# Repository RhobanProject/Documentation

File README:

The full documentation is managed here :
https://sites.google.com/site/rhobanyeosuproject/

It will be moved here later

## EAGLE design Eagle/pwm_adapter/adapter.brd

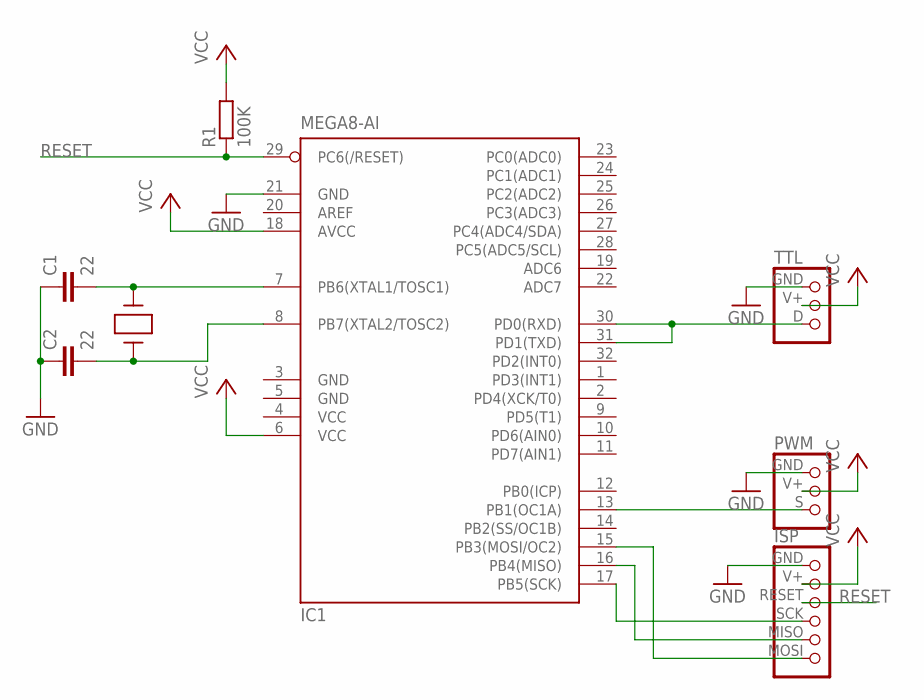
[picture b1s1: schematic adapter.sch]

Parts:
C1, C2: 22; C0603
IC1: MEGA8-AI; TQFP32-08
ISP: CONNEC_1X06_AVRISP; CONNEC_AVRISP
PWM: CONNEC_1X03_PWM; CONNEC_PWM
R1: 100K; R0805
TTL: CONNEC_1X03_TTL; CONNEC_TTL
XTAL: QUARTZ; HC49US

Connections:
DATA: IC1.30 (PD0(RXD)), IC1.31 (PD1(TXD)), TTL.D (3)
GND: C1.1, C2.1, IC1.3 (GND), IC1.5 (GND), IC1.21 (GND), ISP.GND (1), PWM.GND (1), TTL.GND (1)
MISO: IC1.16 (PB4(MISO)), ISP.MISO (5)
MOSI: IC1.15 (PB3(MOSI/OC2)), ISP.MOSI (6)
unnamed: C1.2, IC1.7 (PB6(XTAL1/TOSC1)), XTAL.2
unnamed: C2.2, IC1.8 (PB7(XTAL2/TOSC2)), XTAL.1
OC1A: IC1.13 (PB1(OC1A)), PWM.S (3)
RESET: IC1.29 (PC6(/RESET)), ISP.RESET (3), R1.1
SCK: IC1.17 (PB5(SCK)), ISP.SCK (4)
VCC: IC1.4 (VCC), IC1.6 (VCC), IC1.18 (AVCC), ISP.V+ (2), PWM.V+ (2), R1.2, TTL.V+ (2)

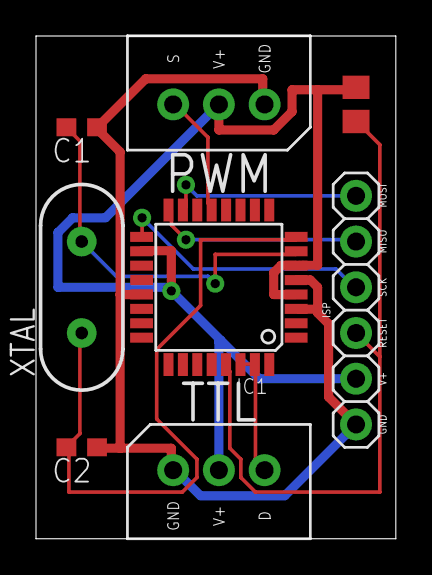
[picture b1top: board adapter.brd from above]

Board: 2 copper layers, 20.0 x 27.9 mm, 8 parts (0 on the bottom side), 10 nets.

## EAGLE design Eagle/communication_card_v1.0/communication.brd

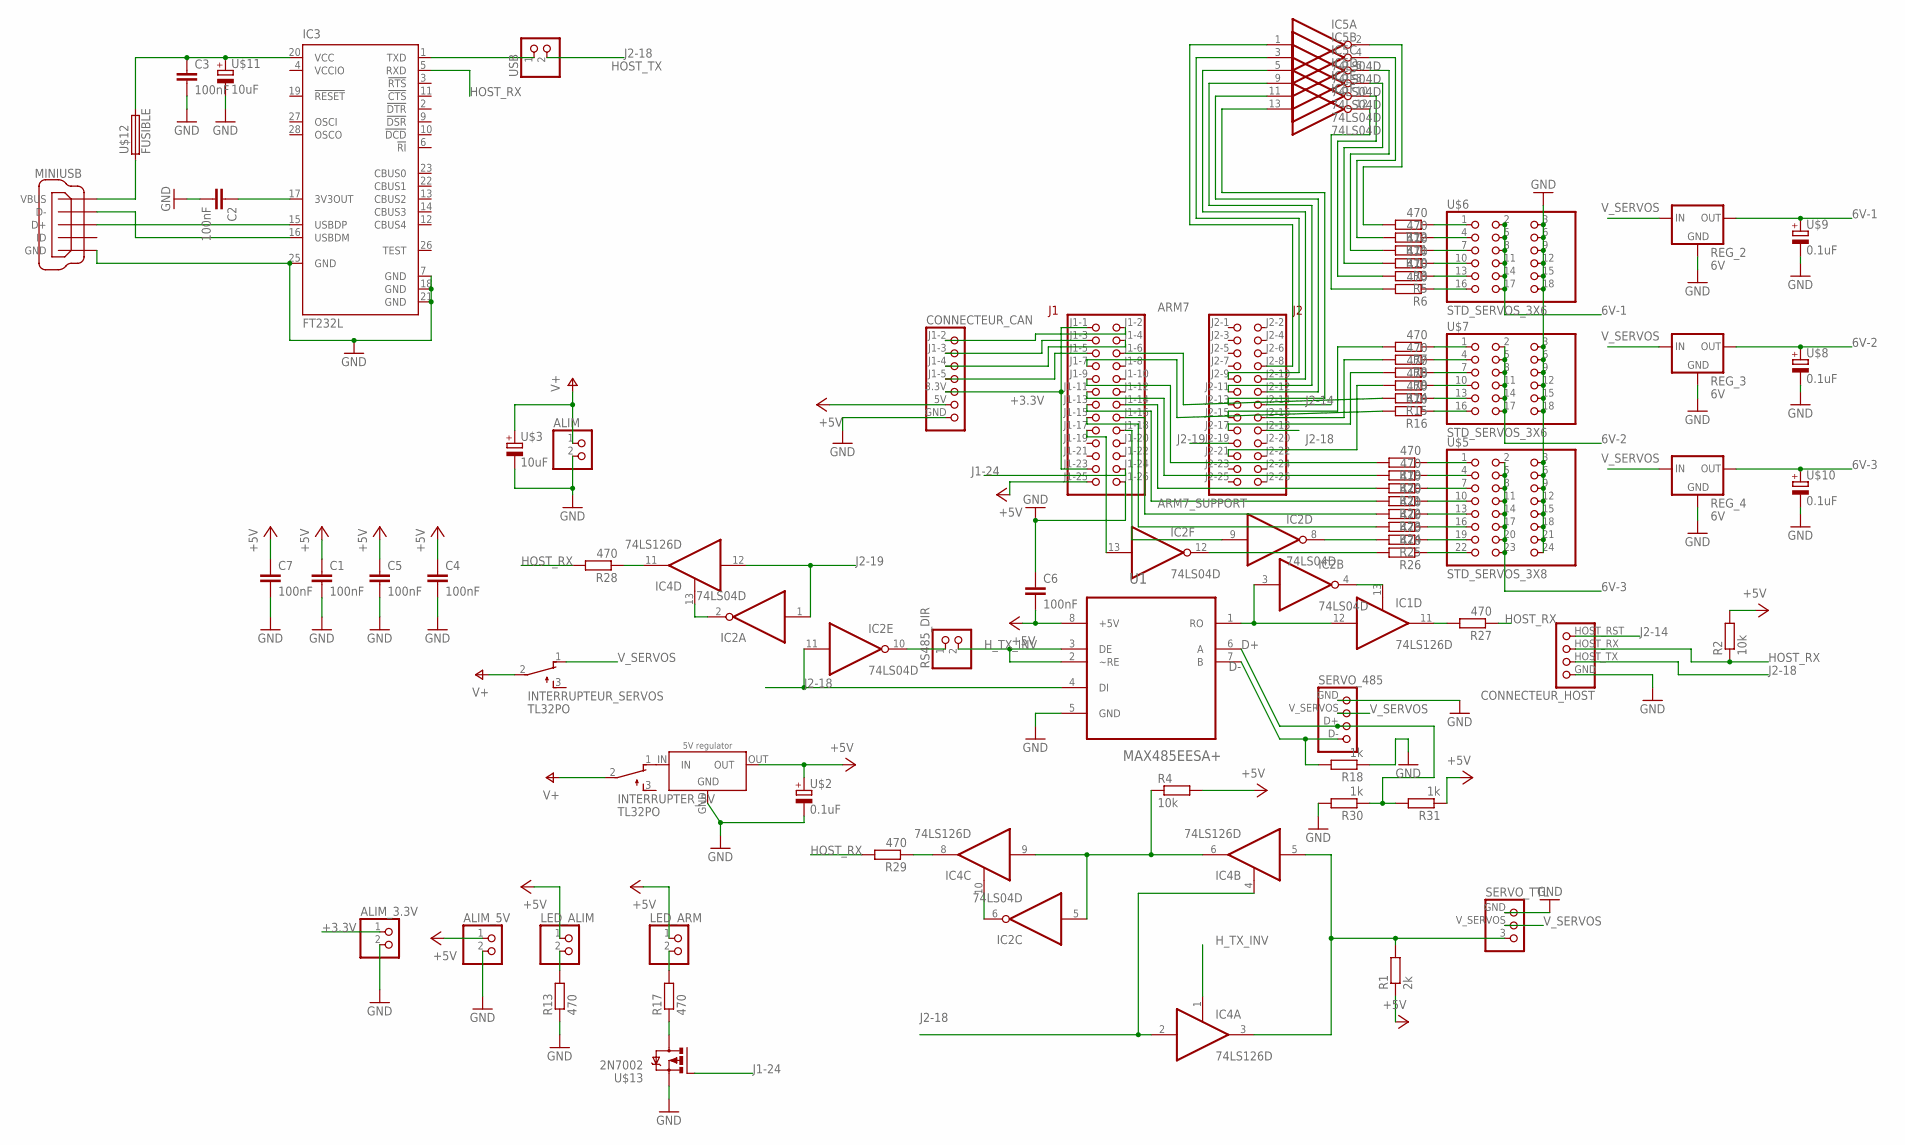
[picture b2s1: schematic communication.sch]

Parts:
ALIM: CONNEC_1X02
ALIM_3.3V, ALIM_5V: CONNEC_1X02
ARM7: ARM7_SUPPORT
C1, C2, C3, C4, C5, C6, C7: 100nF; C1210
CONNECTEUR_CAN: CONNECTEUR_CAN
CONNECTEUR_HOST: CONNECTEUR_HOST
IC1, IC4: 74LS126D; SO14
IC2, IC5: 74LS04D; SO14
IC3: FT232L; SSOP28
INTERRUPTER_5V: TL32PO; TL3XPO
INTERRUPTEUR_SERVOS: TL32PO; TL3XPO
LED_ALIM: CONNEC_1X02
LED_ARM: CONNEC_1X02
MINIUSB: MINIUSB; MINI_USB
R1: 2k; R0805
R2, R4: 10k; R0805
R3, R5, R6, R7, R8, R9, R10, R11, R12, R13, R14, R15, R16, R17, R19, R20, R21, R22, R23, R24, R25, R26, R27, R28, R29: 470; R0805
R18, R30, R31: 1k; R0805
REG_2, REG_3, REG_4: 6V; 78XXL
RS485_DIR: CONNEC_1X02
SERVO_485: CONNECTEUR_485
SERVO_TTL: CONNECTEUR_TTL
U1: MAX485EESA+; SOIC127P600X175-8N
U$2, U$8, U$9, U$10: 0.1uF; E2,5-6
U$3, U$11: 10uF; E5-10,5
U$5: STD_SERVOS_3X8
U$6, U$7: STD_SERVOS_3X6
U$12: FUSIBLE
U$13: 2N7002; SOT23
U$14: 5V regulator; REGULATEUR_CMS
USB: CONNEC_1X02

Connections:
6V-1: REG_2.OUT, U$6.2, U$6.5, U$6.8, U$6.11, U$6.14, U$6.17, U$9.+
6V-2: REG_3.OUT, U$7.2, U$7.5, U$7.8, U$7.11, U$7.14, U$7.17, U$8.+
6V-3: REG_4.OUT, U$5.2, U$5.5, U$5.8, U$5.11, U$5.14, U$5.17, U$5.20, U$5.23, U$10.+
+3.3V: ALIM_3.3V.1, ARM7.J1-1 (1), ARM7.J1-23 (23), CONNECTEUR_CAN.3.3V
+5V: ALIM_5V.1, ARM7.J1-25 (25), C1.1, C4.1, C5.1, C6.2, C7.1, CONNECTEUR_CAN.5V, IC1.14 (+5V), IC2.14 (+5V), IC4.14 (+5V), IC5.14 (+5V), LED_ALIM.1, LED_ARM.1, R1.1, R2.2, R4.2, R31.1, U1.8 (+5V), U$2.+, U$14.OUT
ALIM_USB: C3.1, IC3.20 (VCC), U$11.+, U$12.P$2 (2)
B$1: ARM7.J2-8 (34), IC5.1 (I)
B$2: ARM7.J2-9 (35), IC5.3 (I)
B$3: ARM7.J2-10 (36), IC5.5 (I)
B$4: ARM7.J2-11 (37), IC5.9 (I)
B$5: ARM7.J2-12 (38), IC5.11 (I)
B$6: ARM7.J2-13 (39), IC5.13 (I)
B$7: ARM7.J2-15 (41), R7.2
B$8: ARM7.J2-16 (42), R8.2
B$9: ARM7.J2-17 (43), R9.2
B$10: ARM7.J2-21 (47), R14.2
B$11: ARM7.J1-6 (6), R15.2
B$12: ARM7.J1-7 (7), R16.2
D+: R30.1, R31.2, SERVO_485.D+, U1.6 (A)
D-: R18.2, SERVO_485.D-, U1.7 (B)
GND: ALIM.2, ALIM_3.3V.2, ALIM_5V.2, ARM7.J1-26 (26), C1.2, C2.2, C3.2, C4.2, C5.2, C6.1, C7.2, CONNECTEUR_CAN.GND, CONNECTEUR_HOST.GND, IC1.7 (GND), IC2.7 (GND), IC3.7 (GND), IC3.18 (GND), IC3.21 (GND), IC3.25 (GND), IC4.7 (GND), IC5.7 (GND), MINIUSB.GND, R13.1, R18.1, R30.2, REG_2.GND, REG_3.GND, REG_4.GND, SERVO_485.GND, SERVO_TTL.GND, U1.5 (GND), U$2.-, U$3.-, U$5.3, U$5.6, U$5.9, U$5.12, U$5.15, U$5.18, U$5.21, U$5.24, U$6.3, U$6.6, U$6.9, U$6.12, U$6.15, U$6.18, U$7.3, U$7.6, U$7.9, U$7.12, U$7.15, U$7.18, U$8.-, U$9.-, U$10.-, U$11.-, U$13.2 (S), U$14.GND, U$14.GND2 (GND)
HOST_RX: CONNECTEUR_HOST.HOST_RX, IC3.5 (RXD), R2.1, R27.1, R28.2, R29.2
H_TX_INV: IC4.1 (OE), RS485_DIR.2, U1.2 (~RE), U1.3 (DE)
J1-2: ARM7.J1-2 (2), CONNECTEUR_CAN.J1-2
J1-3: ARM7.J1-3 (3), CONNECTEUR_CAN.J1-3
J1-4: ARM7.J1-4 (4), CONNECTEUR_CAN.J1-4
J1-5: ARM7.J1-5 (5), CONNECTEUR_CAN.J1-5
J1-24: ARM7.J1-24 (24), U$13.1 (G)
J2-14: ARM7.J2-14 (40), CONNECTEUR_HOST.HOST_RST
J2-18: ARM7.J2-18 (44), CONNECTEUR_HOST.HOST_TX, IC2.11 (I), IC4.2 (I), IC4.4 (OE), U1.4 (DI), USB.2
J2-19: ARM7.J2-19 (45), IC2.1 (I), IC4.12 (I)
unnamed: IC2.6 (O), IC4.10 (OE)
unnamed: IC2.5 (I), IC4.6 (O), IC4.9 (I), R4.1
unnamed: INTERRUPTER_5V.1 (O), U$14.IN
unnamed: IC2.8 (O), R25.2
unnamed: IC4.3 (O), IC4.5 (I), R1.2, SERVO_TTL.3
unnamed: LED_ALIM.2, R13.2
unnamed: IC1.12 (I), IC2.3 (I), U1.1 (RO)
unnamed: IC2.12 (O), R26.2
unnamed: R17.1, U$13.3 (D)
unnamed: LED_ARM.2, R17.2
unnamed: IC3.1 (TXD), USB.1
unnamed: IC1.13 (OE), IC2.4 (O)
unnamed: ARM7.J1-9 (9), R19.2
unnamed: MINIUSB.VBUS, U$12.P$1 (1)
unnamed: IC2.2 (O), IC4.13 (OE)
unnamed: R12.1, U$6.1
unnamed: R11.1, U$6.4
unnamed: R10.1, U$6.7
unnamed: R3.1, U$6.10
unnamed: R5.1, U$6.13
unnamed: R6.1, U$6.16
unnamed: R7.1, U$7.1
unnamed: R8.1, U$7.4
unnamed: R9.1, U$7.7
unnamed: R14.1, U$7.10
unnamed: R15.1, U$7.13
unnamed: R16.1, U$7.16
unnamed: ARM7.J1-11 (11), R20.2
unnamed: ARM7.J1-13 (13), R22.2
unnamed: ARM7.J1-14 (14), R21.2
unnamed: ARM7.J1-16 (16), R23.2
unnamed: ARM7.J1-15 (15), R24.2
unnamed: ARM7.J1-18 (18), IC2.9 (I)
unnamed: ARM7.J1-17 (17), IC2.13 (I)
unnamed: R19.1, U$5.1
unnamed: R20.1, U$5.4
unnamed: R21.1, U$5.7
unnamed: R22.1, U$5.10
unnamed: R23.1, U$5.13
unnamed: R24.1, U$5.16
unnamed: R25.1, U$5.19
unnamed: R26.1, U$5.22
unnamed: IC2.10 (O), RS485_DIR.1
unnamed: C2.1, IC3.17 (3V3OUT)
unnamed: IC3.15 (USBDP), MINIUSB.D+
unnamed: IC3.16 (USBDM), MINIUSB.D-
unnamed: IC5.12 (O), R6.2
unnamed: IC5.10 (O), R5.2
unnamed: IC5.8 (O), R3.2
unnamed: IC5.6 (O), R10.2
unnamed: IC5.4 (O), R11.2
unnamed: IC5.2 (O), R12.2
TO_RX-1: IC1.11 (O), R27.2
TO_RX-2: IC4.8 (O), R29.1
TO_RX-3: IC4.11 (O), R28.1
V+: ALIM.1, INTERRUPTER_5V.2, INTERRUPTEUR_SERVOS.2, U$3.+
VCCIO: IC3.4 (VCCIO)
V_SERVOS: INTERRUPTEUR_SERVOS.1 (O), REG_2.IN, REG_3.IN, REG_4.IN, SERVO_485.V_SERVOS, SERVO_TTL.V_SERVOS

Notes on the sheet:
HOST_TX

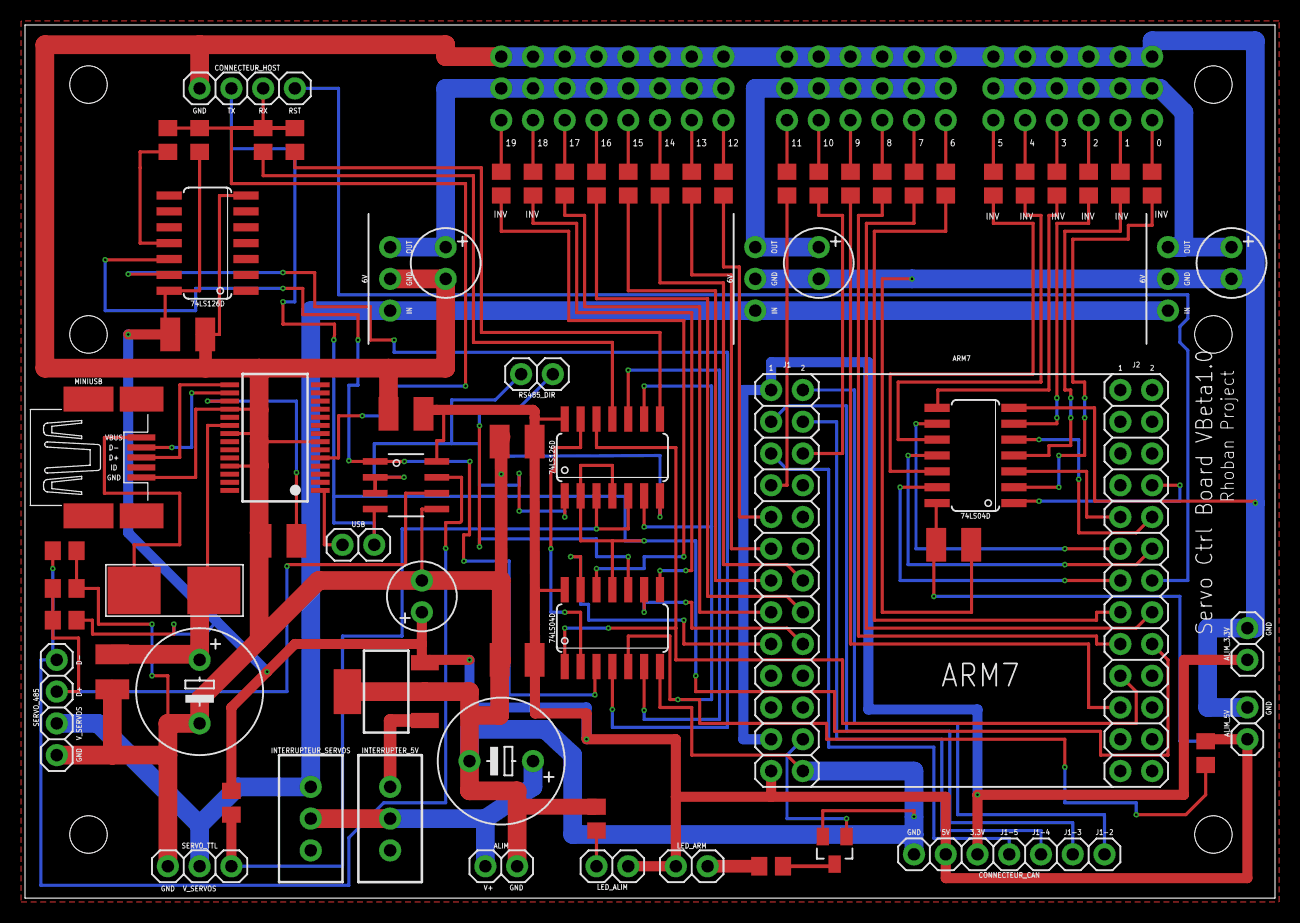
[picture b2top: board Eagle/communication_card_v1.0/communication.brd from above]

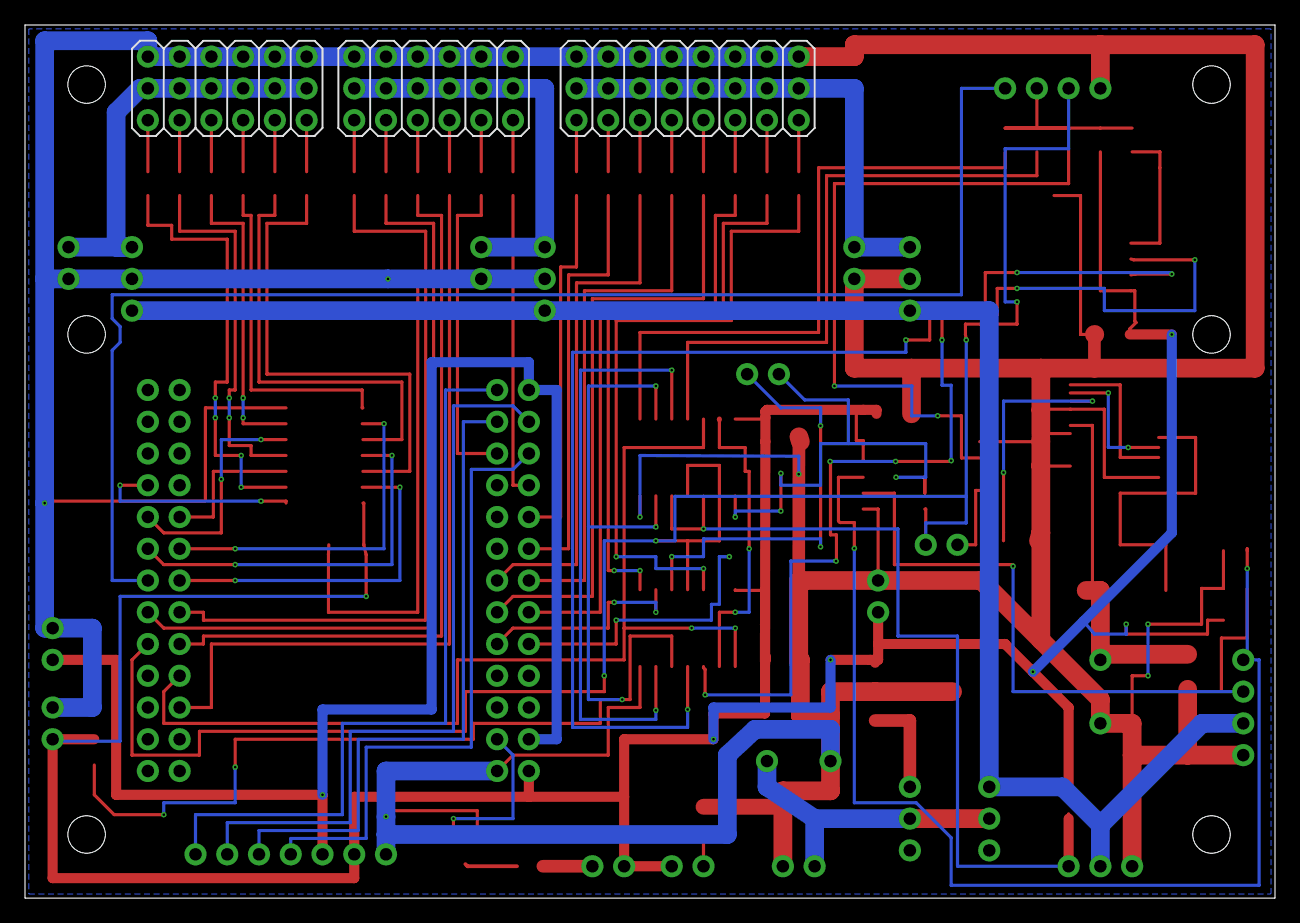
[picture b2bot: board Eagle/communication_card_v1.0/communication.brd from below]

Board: 2 copper layers, 100.0 x 69.9 mm, 74 parts (3 on the bottom side), 88 nets.

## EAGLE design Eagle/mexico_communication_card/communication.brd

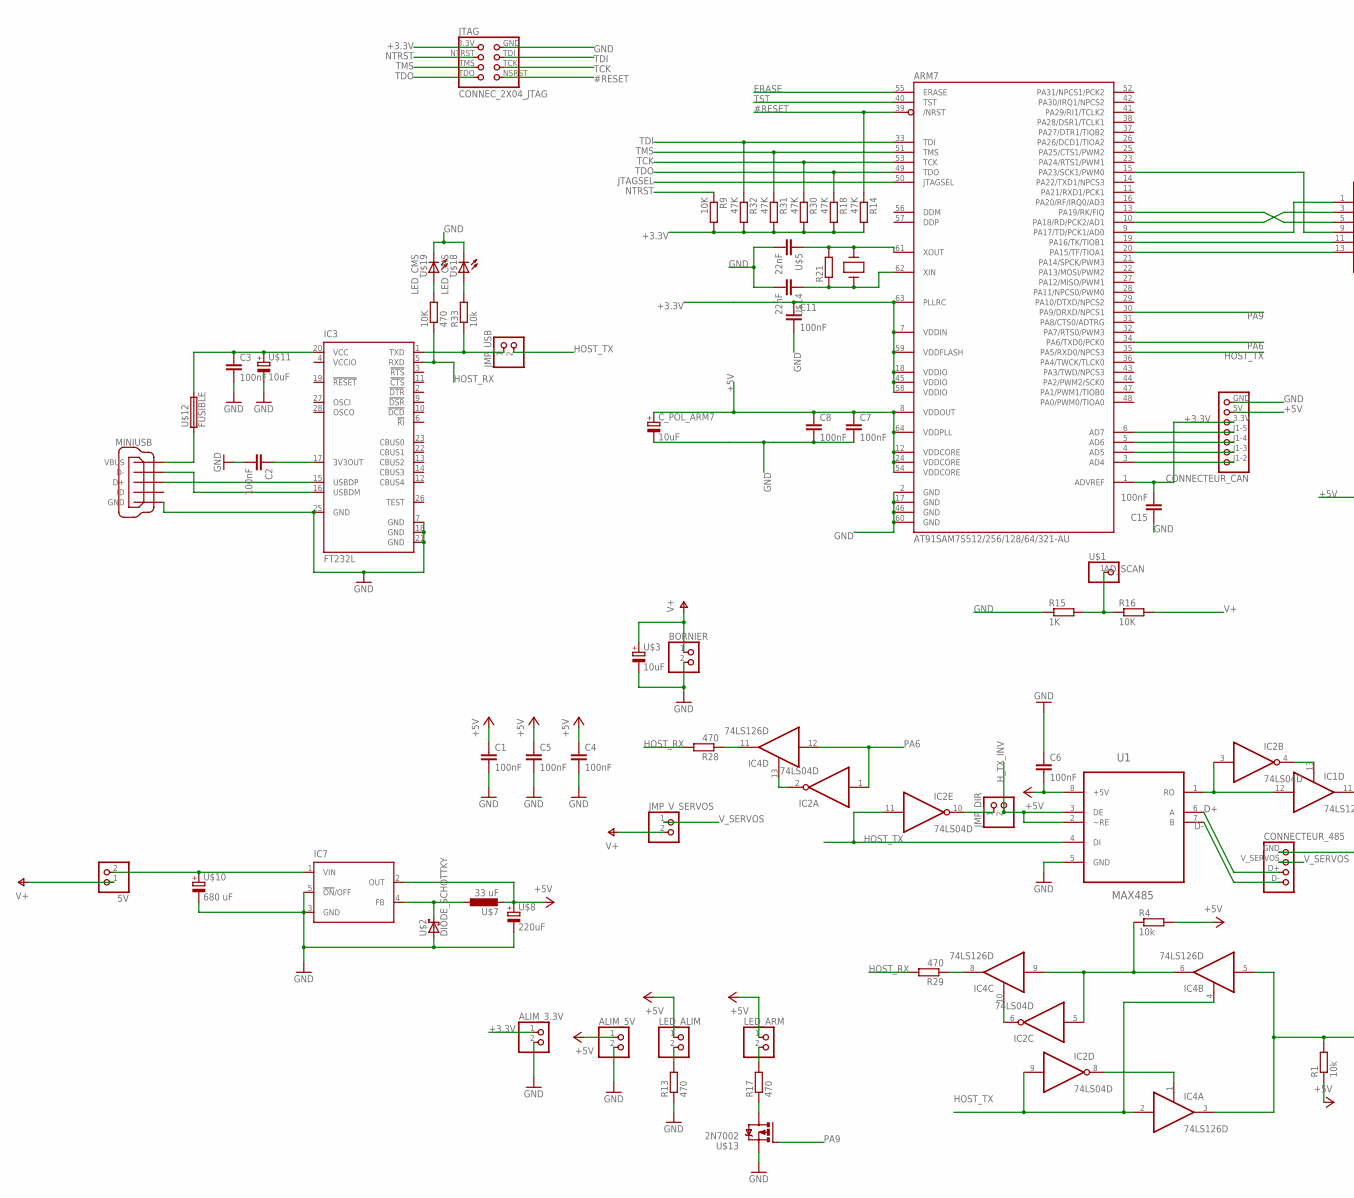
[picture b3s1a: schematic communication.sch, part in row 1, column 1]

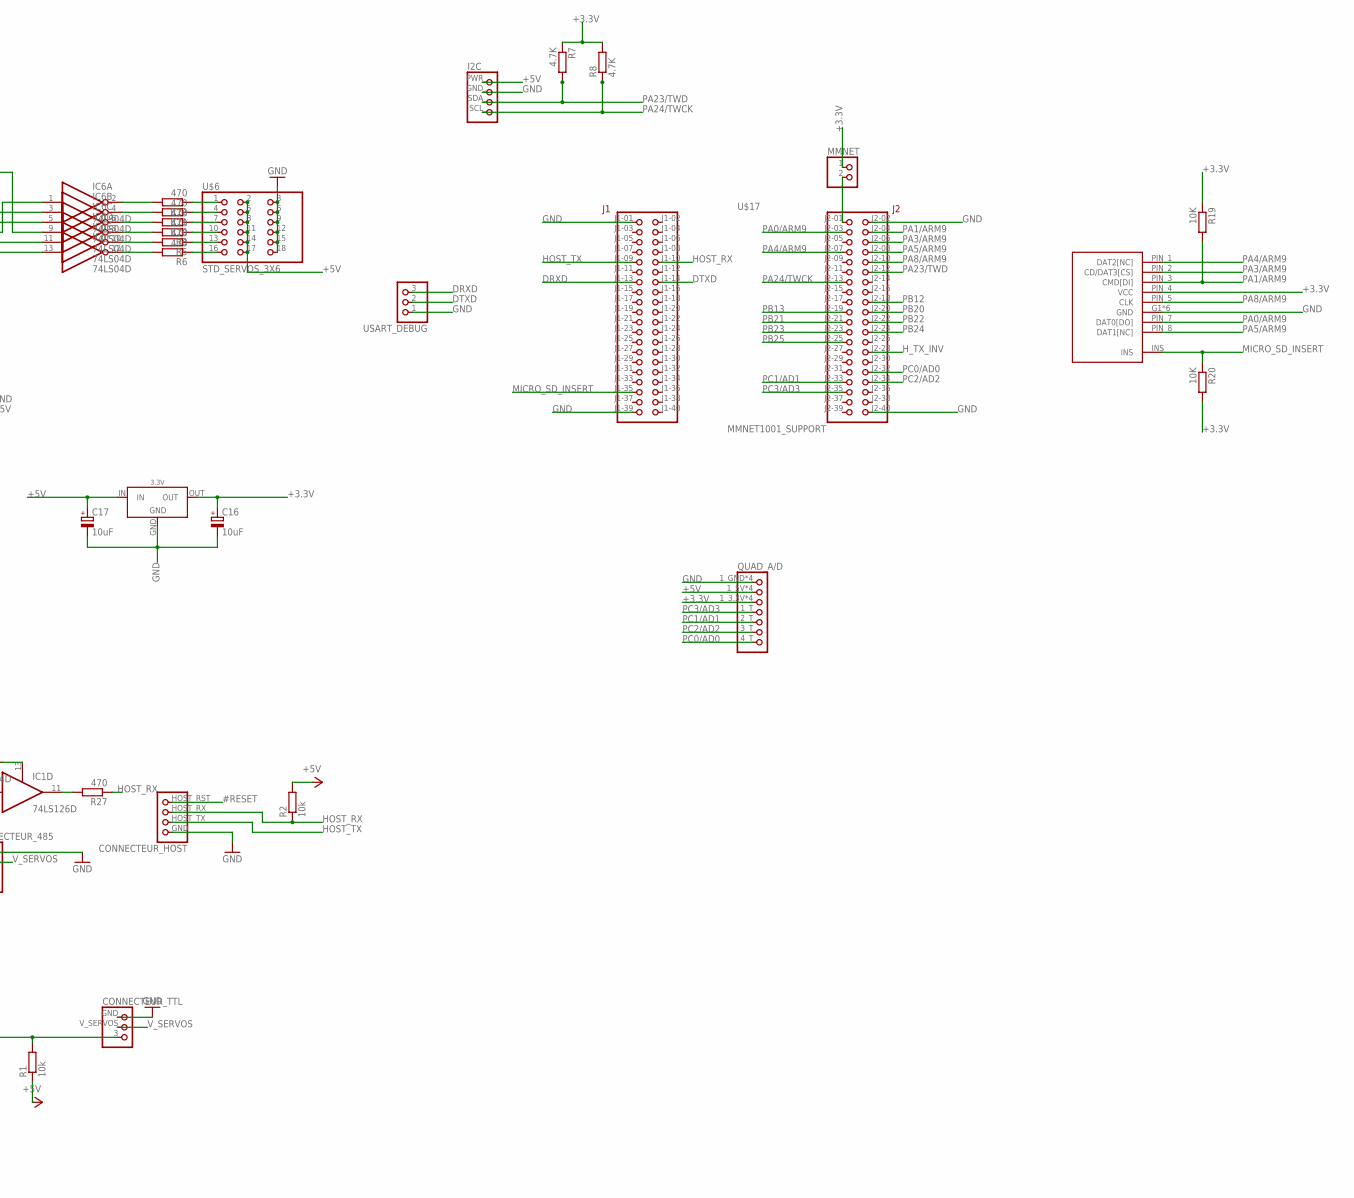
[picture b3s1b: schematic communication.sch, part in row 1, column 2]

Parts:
5V: CONNEC_1X02CONNEC_1X02_LARGE; CONNEC_ALIM
10K: 470; R0805@1
ALIM_3.3V, ALIM_5V: CONNEC_1X02
ARM7: AT91SAM7S512/256/128/64/321-AU; LQFP64
BORNIER: CONNEC_1X02CONNEC_1X02_LARGE; CONNEC_ALIM
C1, C2, C3, C4, C5, C6, C7, C8, C11, C15: 100nF; C0805
C16, C17: 10uF; PANASONIC_B
CONNECTEUR_485: CONNECTEUR_485
CONNECTEUR_CAN: CONNECTOR_CAN
CONNECTEUR_HOST: CONNECTEUR_HOST
CONNECTEUR_TTL: CONNECTEUR_TTL
C_POL_ARM7: 10uF; PANASONIC_B
I2C: CONNEC_1X04_I2C; CONNEC_I2C
IC1, IC4: 74LS126D; SO14
IC2, IC6: 74LS04D; SO14
IC3: FT232L; SSOP28
IC7: LM2596S; TO263-5
JMP_DIR: CONNEC_1X02
JMP_USB: CONNEC_1X02
JMP_V_SERVOS: CONNEC_1X02CONNEC_1X02_LARGE; CONNEC_ALIM
JTAG: CONNEC_2X04_JTAG; CONNEC_JTAG_MINIMAL
LED_ALIM: CONNEC_1X02
LED_ARM: CONNEC_1X02
MINIUSB: MINIUSB; MINI_USB
MMNET: CONNEC_1X02CONNEC_1X02_LARGE; CONNEC_ALIM
QUAD_A/D: QUAD_A/D
R1, R2, R4, R33: 10k; R0805@1
R3, R5, R6, R10, R11, R12, R13, R17, R27, R28, R29: 470; R0805@1
R7, R8: 4.7K; R0805@1
R9, R16, R19, R20: 10K; R0805@1
R14, R18, R30, R31, R32: 47K; R0805@1
R15: 1K; R0805@1
R21: RESISTANCE-1MOHM; R0805
U1: MAX485; SO8
U$1: CONNEC_1X01
U$2: DIODE_SCHOTTKY; SOD123W
U$3, U$11: 10uF; PANASONIC_B
U$4: 18.432 Mhz; ABLS
U$5, U$14: 22nF; C0603
U$6: STD_SERVOS_3X6
U$7: 33 uF; SDC0604
U$8: 220uF; E3,5-8
U$9: MICRO_SD
U$10: 680 uF; E3,5-8
U$12: FUSIBLE
U$13: 2N7002; SOT23
U$15: 3.3V; REGULATEUR_CMS
U$17: MMNET1001_SUPPORT; MMNET01_SUPPORT
U$18, U$19: LED_CMS
USART_DEBUG: CONNEC_1X03

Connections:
#RESET: ARM7.39 (/NRST), CONNECTEUR_HOST.HOST_RST, JTAG.NSRST (8), R14.1
+3.3V: ALIM_3.3V.1, ARM7.1 (ADVREF), ARM7.7 (VDDIN), ARM7.18 (VDDIO), ARM7.45 (VDDIO), ARM7.58 (VDDIO), ARM7.59 (VDDFLASH), ARM7.63 (PLLRC), C11.1, C15.2, C16.+, CONNECTEUR_CAN.3.3V, JTAG.3.3V (1), MMNET.1, QUAD_A/D.1_3.3V (3), QUAD_A/D.2_3.3V (3), QUAD_A/D.3_3.3V (3), QUAD_A/D.4_3.3V (3), R7.1, R8.2, R9.2, R14.2, R18.2, R19.1, R20.2, R30.2, R31.2, R32.2, U$9.PIN_4 (VCC), U$15.OUT
+5V: ALIM_5V.1, ARM7.8 (VDDOUT), ARM7.12 (VDDCORE), ARM7.24 (VDDCORE), ARM7.54 (VDDCORE), ARM7.64 (VDDPLL), C1.1, C4.1, C5.1, C6.2, C7.1, C8.1, C17.+, CONNECTEUR_CAN.5V, C_POL_ARM7.+, I2C.PWR (1), IC1.14 (+5V), IC2.14 (+5V), IC4.14 (+5V), IC6.14 (+5V), IC7.2 (OUT), LED_ALIM.1, LED_ARM.1, QUAD_A/D.1_5V (2), QUAD_A/D.2_5V (2), QUAD_A/D.3_5V (2), QUAD_A/D.4_5V (2), R1.1, R2.2, R4.2, U1.8 (+5V), U$6.2, U$6.5, U$6.8, U$6.11, U$6.14, U$6.17, U$7.P$2 (2), U$8.+, U$15.IN
AD_SCAN: R15.2, R16.1, U$1.1
ALIM_USB: C3.1, IC3.20 (VCC), U$11.+, U$12.P$2 (2)
D+: CONNECTEUR_485.D+, U1.6 (A)
D-: CONNECTEUR_485.D-, U1.7 (B)
DRXD: U$17.J1-13, USART_DEBUG.3
DTXD: U$17.J1-14, USART_DEBUG.2
ERASE: ARM7.55 (ERASE)
GND: ALIM_3.3V.2, ALIM_5V.2, ARM7.2 (GND), ARM7.17 (GND), ARM7.46 (GND), ARM7.60 (GND), BORNIER.2, C1.2, C2.2, C3.2, C4.2, C5.2, C6.1, C7.2, C8.2, C11.2, C15.1, C16.-, C17.-, CONNECTEUR_485.GND, CONNECTEUR_CAN.GND, CONNECTEUR_HOST.GND, CONNECTEUR_TTL.GND, C_POL_ARM7.-, I2C.GND (2), IC1.7 (GND), IC2.7 (GND), IC3.7 (GND), IC3.18 (GND), IC3.21 (GND), IC3.25 (GND), IC4.7 (GND), IC6.7 (GND), IC7.3 (GND), IC7.5 (!ON!/OFF), JTAG.GND (2), MINIUSB.GND, QUAD_A/D.1_GND (1), QUAD_A/D.2_GND (1), QUAD_A/D.3_GND (1), QUAD_A/D.4_GND (1), R13.1, R15.1, U1.5 (GND), U$2.A, U$3.-, U$5.2, U$6.3, U$6.6, U$6.9, U$6.12, U$6.15, U$6.18, U$8.-, U$9.G1 (GND), U$9.G2 (GND), U$9.G3 (GND), U$9.G5 (GND), U$9.G6 (GND), U$9.PIN_6 (GND), U$10.-, U$11.-, U$13.2 (S), U$14.2, U$15.GND, U$15.GND2 (GND), U$17.J1-01, U$17.J1-39, U$17.J2-02, U$17.J2-40, U$18.1 (C), U$19.1 (C), USART_DEBUG.1
HOST_RX: 10K.1, CONNECTEUR_HOST.HOST_RX, IC3.5 (RXD), R2.1, R27.1, R28.2, R29.2, U$17.J1-10
HOST_TX: ARM7.35 (PA5/RXD0/NPCS3), CONNECTEUR_HOST.HOST_TX, IC2.9 (I), IC2.11 (I), IC4.2 (I), IC4.4 (OE), JMP_USB.2, U1.4 (DI), U$17.J1-09
H_TX_INV: JMP_DIR.2, U1.2 (~RE), U1.3 (DE), U$17.J2-28
J1-2: ARM7.3 (AD4), CONNECTEUR_CAN.J1-2
J1-3: ARM7.4 (AD5), CONNECTEUR_CAN.J1-3
J1-4: ARM7.5 (AD6), CONNECTEUR_CAN.J1-4
J1-5: ARM7.6 (AD7), CONNECTEUR_CAN.J1-5
JTAGSEL: ARM7.50 (JTAGSEL)
MICRO_SD_INSERT: R20.1, U$9.INS, U$17.J1-35
unnamed: IC2.6 (O), IC4.10 (OE)
unnamed: IC2.5 (I), IC4.6 (O), IC4.9 (I), R4.1
unnamed: 5V.2, IC7.1 (VIN), U$10.+
unnamed: IC2.8 (O), IC4.1 (OE)
unnamed: CONNECTEUR_TTL.3, IC4.3 (O), IC4.5 (I), R1.2
unnamed: LED_ALIM.2, R13.2
unnamed: IC1.12 (I), IC2.3 (I), U1.1 (RO)
unnamed: ARM7.62 (XIN), R21.1, U$4.P$2 (1), U$14.1
unnamed: R17.1, U$13.3 (D)
unnamed: LED_ARM.2, R17.2
unnamed: IC3.1 (TXD), JMP_USB.1, R33.1
unnamed: IC1.13 (OE), IC2.4 (O)
unnamed: R33.2, U$18.2 (A)
unnamed: MINIUSB.VBUS, U$12.P$1 (1)
unnamed: IC2.2 (O), IC4.13 (OE)
unnamed: R12.1, U$6.1
unnamed: R11.1, U$6.4
unnamed: R10.1, U$6.7
unnamed: R3.1, U$6.10
unnamed: R5.1, U$6.13
unnamed: R6.1, U$6.16
unnamed: IC6.2 (O), R12.2
unnamed: IC6.4 (O), R11.2
unnamed: IC6.6 (O), R10.2
unnamed: IC6.8 (O), R3.2
unnamed: IC6.10 (O), R5.2
unnamed: IC6.12 (O), R6.2
unnamed: 10K.2, U$19.2 (A)
unnamed: IC7.4 (FB), U$2.C, U$7.P$1 (1)
unnamed: IC2.10 (O), JMP_DIR.1
unnamed: MMNET.2, U$17.J2-01
unnamed: ARM7.61 (XOUT), R21.2, U$4.P$1 (2), U$5.1
unnamed: C2.1, IC3.17 (3V3OUT)
unnamed: IC3.15 (USBDP), MINIUSB.D+
unnamed: IC3.16 (USBDM), MINIUSB.D-
unnamed: ARM7.20 (PA15/TF/TIOA1), IC6.13 (I)
unnamed: ARM7.19 (PA16/TK/TIOB1), IC6.11 (I)
unnamed: ARM7.15 (PA23/SCK1/PWM0), IC6.9 (I)
unnamed: ARM7.13 (PA19/RK/FIQ), IC6.5 (I)
unnamed: ARM7.10 (PA18/RD/PCK2/AD1), IC6.3 (I)
unnamed: ARM7.9 (PA17/TD/PCK1/AD0), IC6.1 (I)
NTRST: JTAG.NTRST (3), R9.1
PA0/ARM9: U$9.PIN_7 (DAT0[DO]), U$17.J2-03
PA1/ARM9: R19.2, U$9.PIN_3 (CMD[DI]), U$17.J2-04
PA3/ARM9: U$9.PIN_2 (CD/DAT3[CS]), U$17.J2-06
PA4/ARM9: U$9.PIN_1 (DAT2[NC]), U$17.J2-07
PA5/ARM9: U$9.PIN_8 (DAT1[NC]), U$17.J2-08
PA6: ARM7.34 (PA6/TXD0/PCK0), IC2.1 (I), IC4.12 (I)
PA8/ARM9: U$9.PIN_5 (CLK), U$17.J2-10
PA9: ARM7.30 (PA9/DRXD/NPCS1), U$13.1 (G)
PA23/TWD: I2C.SDA (3), R7.2, U$17.J2-12
PA24/TWCK: I2C.SCL (4), R8.1, U$17.J2-13
PB12: U$17.J2-18
PB13: U$17.J2-19
PB20: U$17.J2-20
PB21: U$17.J2-21
PB22: U$17.J2-22
PB23: U$17.J2-23
PB24: U$17.J2-24
PB25: U$17.J2-25
PC0/AD0: QUAD_A/D.4_T (7), U$17.J2-32
PC1/AD1: QUAD_A/D.2_T (5), U$17.J2-33
PC2/AD2: QUAD_A/D.3_T (6), U$17.J2-34
PC3/AD3: QUAD_A/D.1_T (4), U$17.J2-35
TCK: ARM7.53 (TCK), JTAG.TCK (6), R30.1
TDI: ARM7.33 (TDI), JTAG.TDI (4), R32.1
TDO: ARM7.49 (TDO), JTAG.TDO (7), R18.1
TMS: ARM7.51 (TMS), JTAG.TMS (5), R31.1
TO_RX-1: IC1.11 (O), R27.2
TO_RX-2: IC4.8 (O), R29.1
TO_RX-3: IC4.11 (O), R28.1
TST: ARM7.40 (TST)
V+: 5V.1, BORNIER.1, JMP_V_SERVOS.2, R16.2, U$3.+
VCCIO: IC3.4 (VCCIO)
V_SERVOS: CONNECTEUR_485.V_SERVOS, CONNECTEUR_TTL.V_SERVOS, JMP_V_SERVOS.1

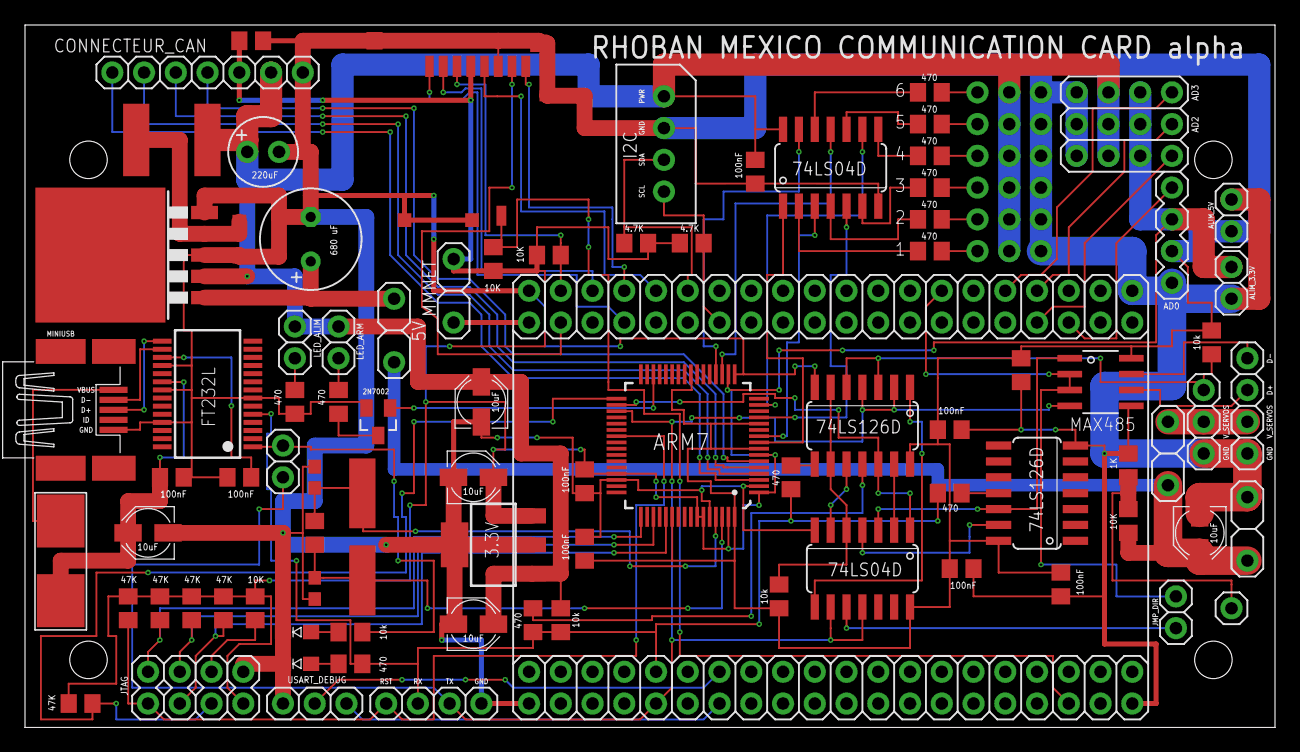
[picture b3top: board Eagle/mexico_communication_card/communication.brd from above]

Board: 2 copper layers, 100.0 x 56.2 mm, 87 parts (1 on the bottom side), 83 nets.

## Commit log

2009-11-05 hugo
2010-12-22 Version 1.0
2011-02-03 added MoveSpec
2011-05-27 first part
2011-05-27 checkpoint
2011-05-30 rien
2011-06-03 rename directory "bootstrap" to "roboard"
2011-06-03 point to me for questions
2011-06-03 add some official doc
2011-06-03 add nice picture
2011-06-03 add RoBoIO library, as distributed by manufacturer
2011-06-03 documentation for the RoBoIO library
2011-06-03 add stuff
2011-06-06 rename servos directory into a generic name, and include the datasheet of the small HD 1900A servo
2011-06-08 add a dmesg for reference
2011-06-14 add scan of doc provided with the torpedo brushless controller
2011-07-12 update with instructions to build a package from sources
2011-07-12 rename to "linux", in preparation for NetBSD version
2011-07-14 add documentation for the ADC which is present on the roboard
2011-07-20 add support for NetBSD
2011-07-20 out*() have different parameter order in NetBSD than in Linux... Now, this library is tested and works under NetBSD.
2011-08-23 add datasheet of regulator
2011-08-23 add datasheet of this other regulator that we have. Requires two 10uF capacitors
2011-09-05 new file, currently describes how things are wired
2011-10-14 added rx28 manual to docs
2011-10-25 rename so that svn doesn't crash on netbsd. (!) I'll rename the links later.
2011-10-25 update links, following renaming of these files
2011-11-20 ajout des manuels de la radiocommande
2012-05-24 Adding eagle schematics
2012-05-24 [Eagle] Adding PWM Adapter project
2012-05-25 Removed Eagle schematics (moved to a new repository)
2013-04-05 Adding initial content of internDoc
2013-04-07 Adding some start of documentation
2013-04-07 Ignoring emacs temporary files
2013-04-07 Adding tutorial on access to mmnet by using a public key
2013-04-08 Adding tuto about alimentation, U changes and config of Servo
2013-04-08 Ajout tuto connexion MMnet et tuto soudure au four
